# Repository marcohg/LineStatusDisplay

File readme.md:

# Line Status Display
Status indicator from process line encoder

Quadrature encoder signals are captured by a remote modbus rtu 485.  
Modbus client in a embedded pc which sends the data to a graphic output application.

## Add encoder_client simulator
- Script `LineStatusDisplay/fw/encoder_client_01/src/encoder_client.sh` 
- Simulates `/mnt/tmp/encoder_client.status` data for `encoder_gui.py`

## Framework: mount tmpfs, modbus client and Python application
Oct.24/2024  
The init process runs at user (scia) level.  

### Add user `scia` 
- Boot RPi5 as root (marco, pi)
- Add scia:
`marco@raspberry $ sudo useradd -m -c "RPi5 Display" scia`  
use a simple password (will change later)
- Add scia to the following groups: `sudo, audio, video`  
  - `sudo usermod -aG sudo scia`
  - `sudo usermod -aG audio scia`
  - `sudo usermod -aG video scia`

### Allow scia to access the main display
- Boot RPi5
- login ssh to scia, from a host terminal: `ssh scia@192.x.x.x`
- test that scia has sudo operations (like touch /mnt/foo, etc)

#### run raspi-config: `sudo raspi-config`
1. System Options
    - S5. Boot / Auto Login
      - B4. Desktop Autologin (scia has a Desktop GUI)
    - S6. Splash Screen   
      - Yes, splash at boot  (customiza later)
        - `/usr/share/plymouth/themes/pix/splash.png`

### clone LineStatusDisplay
- login scia
- clone repository at /home/scia
  - `git clone https://github.com/marcohg/LineStatusDisplay.git .`
  - project folder is:
    - `/home/scia/LineStatusDisplay`
### install systemd services
  - Change to directory `fw/boot` under project folder
    - First list installed services status using `./list.sh`
    - `sudo ./remove scia` all or `sudo ./remove especific.service`
    - The `./install` will install services for current user

### Monitor Processes initiated bt systemd
- `df -h ` verify the tmpfs mounted partion at `/mnt/tmp`
In this RAM parition, some files are created by the different processes.
- `tail -F /mnt/tmp/encoder_client.status` display the activity of the encoder
 client (ctr-c to end). If the RPi5 communicates with the encoder node, 
 `1729992270,0,71,-2,0,0` 
  - stamp date in seconds since epoch.
  - status, 
  - 0.1 secs tick, 
  - total counts, 
  - delta counts and 
  - frequency.

### Configuration
The file `configuration.json` is created at user's home, WIP

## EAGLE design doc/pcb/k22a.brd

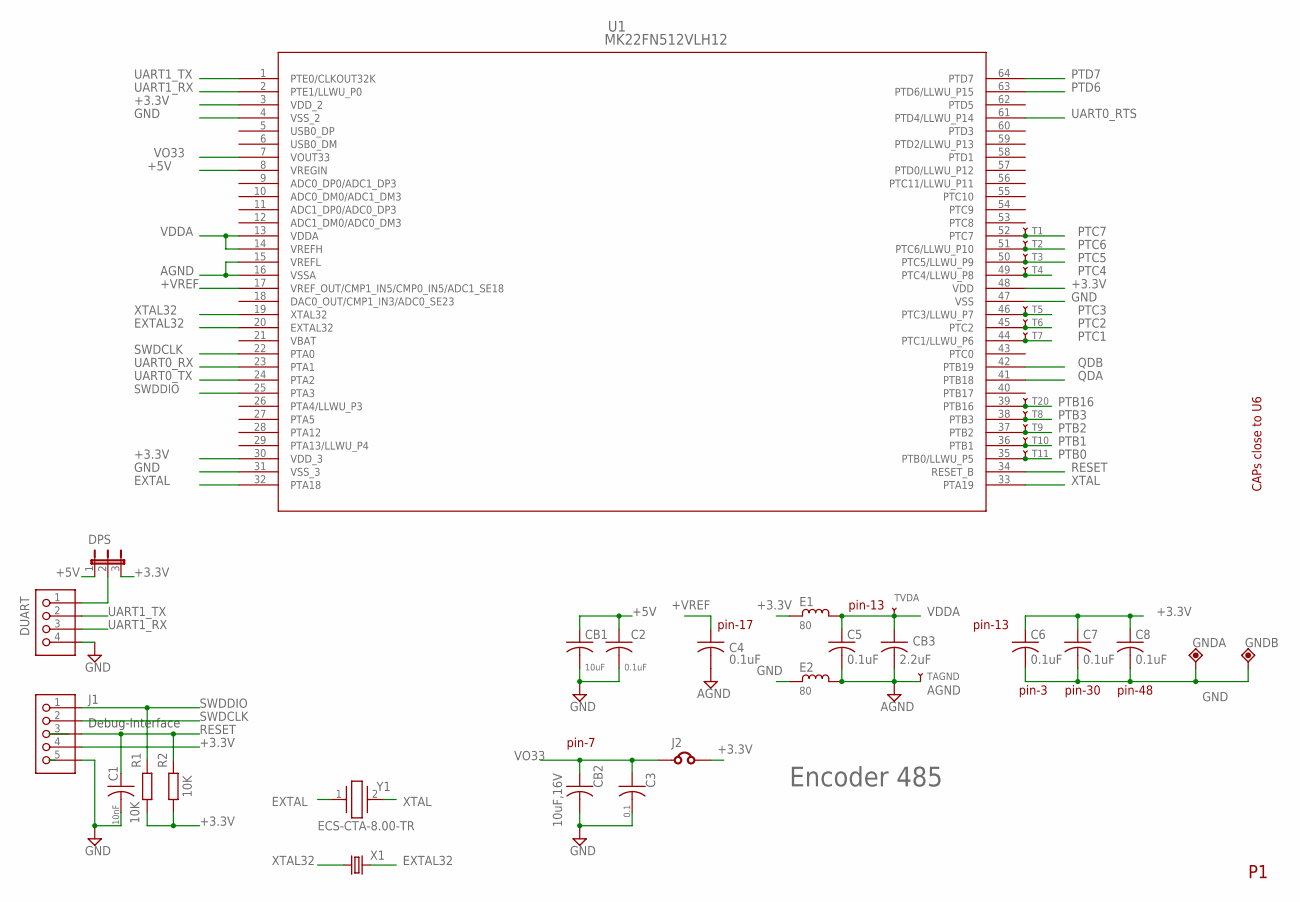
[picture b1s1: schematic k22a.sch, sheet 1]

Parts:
C1: 10nF; C1206
C2, C4, C5, C6, C7, C8: 0.1uF; C1206
C3: 0.1; C1206
CB1: 10uF; C1206
CB2: 10uF,16V; C1206
CB3: 2.2uF; C1206
DPS: JP2E-0805; R0805/2
DUART: PINHD-1X4; 1X4
E1, E2: 80; M1206
GNDA: TPP-PAD-032; PAD-032
GNDB: TPP-PAD-032; PAD-032
J1: PINHD-1X52MM; 1X5_2MM
J2: J0805; R0805
R1, R2: 10K; M1206
T1, T2, T3, T4, T5, T6, T7, T8, T9, T10, T11, T20: ATP-40
TAGND: ATP-40
TVDA: ATP-40
U1: MK22FN512VLH12; LQFP-64_10X10X1.6
X1: CRYSTALTC26V; TC26V@1
Y1: ECS-CTA-8.00-TR; ECSCTA800TR

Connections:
+3.3V: C6.1, C7.1, C8.1, DPS.3, E1.1, J1.4, J2.2, R1.1, R2.1, U1.3 (VDD_2), U1.30 (VDD_3), U1.48 (VDD); also elsewhere on the board
+5V: C2.1, CB1.1, DPS.1, U1.8 (VREGIN); also elsewhere on the board
+VREF: C4.1, U1.17 (VREF_OUT/CMP1_IN5/CMP0_IN5/ADC1_SE18)
AGND: C4.2, C5.2, CB3.2, E2.2, TAGND.P, U1.15 (VREFL), U1.16 (VSSA)
EXTAL: U1.32 (PTA18), Y1.1
EXTAL32: U1.20 (EXTAL32), X1.2
GND: C1.2, C2.2, C3.2, C6.2, C7.2, C8.2, CB1.2, CB2.2, DUART.4, E2.1, GNDA.1, GNDB.1, J1.5, U1.4 (VSS_2), U1.31 (VSS_3), U1.47 (VSS); also elsewhere on the board
unnamed: DPS.2, DUART.1
PTB0: T11.P, U1.35 (PTB0/LLWU_P5)
PTB1: T10.P, U1.36 (PTB1)
PTB2: T9.P, U1.37 (PTB2)
PTB3: T8.P, U1.38 (PTB3)
PTB16: T20.P, U1.39 (PTB16)
PTC1: T7.P, U1.44 (PTC1/LLWU_P6)
PTC2: T6.P, U1.45 (PTC2)
PTC3: T5.P, U1.46 (PTC3/LLWU_P7)
PTC4: T4.P, U1.49 (PTC4/LLWU_P8)
PTC5: T3.P, U1.50 (PTC5/LLWU_P9)
PTC6: T2.P, U1.51 (PTC6/LLWU_P10)
PTC7: T1.P, U1.52 (PTC7)
PTD6: U1.63 (PTD6/LLWU_P15); also elsewhere on the board
PTD7: U1.64 (PTD7); also elsewhere on the board
QDA: U1.41 (PTB18); also elsewhere on the board
QDB: U1.42 (PTB19); also elsewhere on the board
RESET: C1.1, J1.3, R2.2, U1.34 (RESET_B); also elsewhere on the board
SWDCLK: J1.2, U1.22 (PTA0); also elsewhere on the board
SWDDIO: J1.1, R1.2, U1.25 (PTA3); also elsewhere on the board
UART0_RTS: U1.61 (PTD4/LLWU_P14); also elsewhere on the board
UART0_RX: U1.23 (PTA1); also elsewhere on the board
UART0_TX: U1.24 (PTA2); also elsewhere on the board
UART1_RX: DUART.3, U1.2 (PTE1/LLWU_P0)
UART1_TX: DUART.2, U1.1 (PTE0/CLKOUT32K)
VBAT: U1.21 (VBAT)
VDDA: C5.1, CB3.1, E1.2, TVDA.P, U1.13 (VDDA), U1.14 (VREFH)
VO33: C3.1, CB2.1, J2.1, U1.7 (VOUT33)
XTAL: U1.33 (PTA19), Y1.2
XTAL32: U1.19 (XTAL32), X1.1

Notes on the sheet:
Debug-Interface
CAPs close to U6
Encoder 485
pin-13
pin-3
pin-7
pin-48
pin-30
pin-17

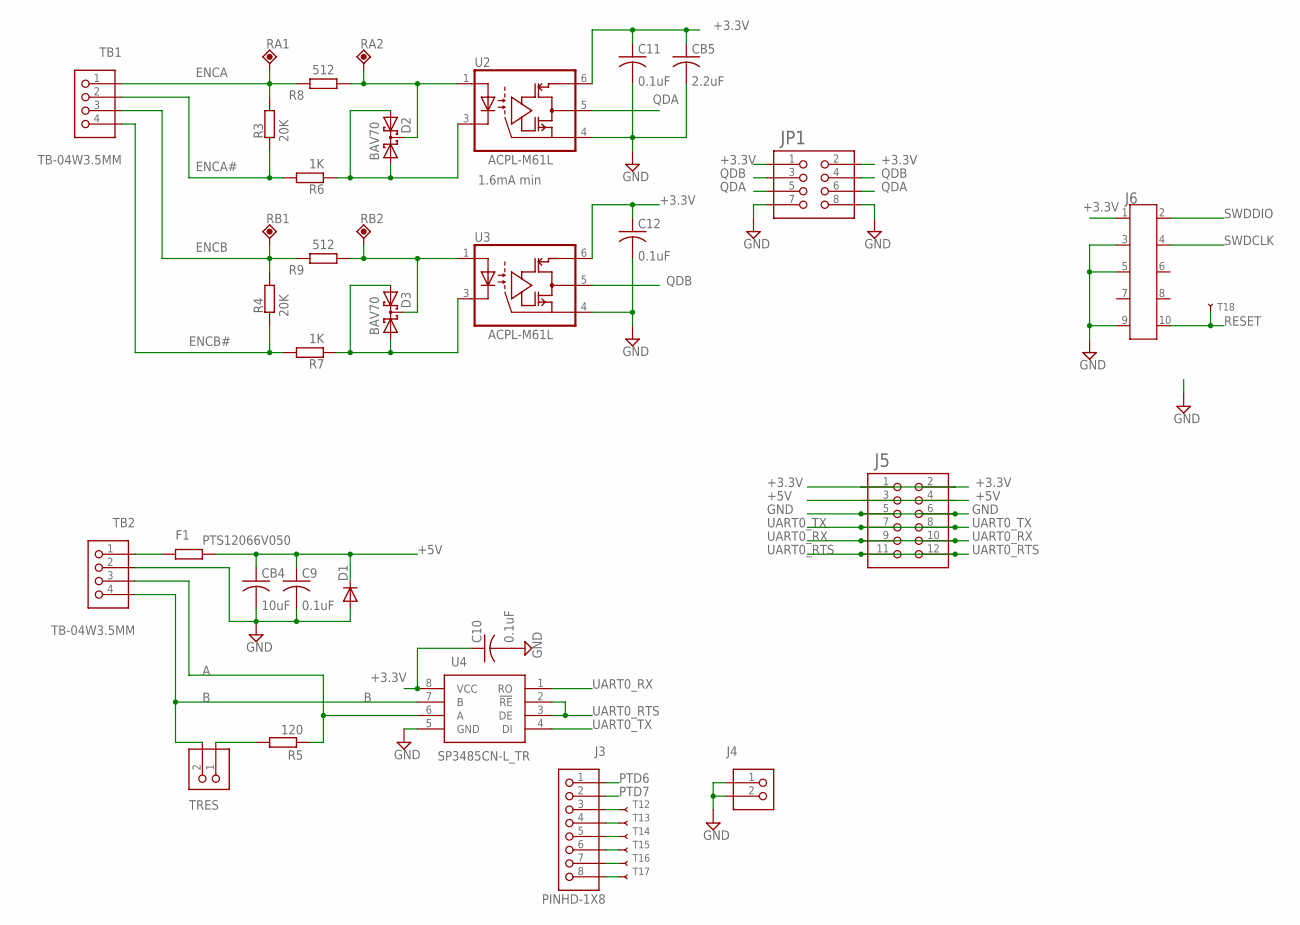
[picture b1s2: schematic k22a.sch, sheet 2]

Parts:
C9, C10, C11, C12: 0.1uF; C1206
CB4: 10uF; C1206
CB5: 2.2uF; C1206
D1: DIODE-DO214AC; DO214AC
D2, D3: BAV70; SOT23; PARTNO BAV70-7-F
F1: PTS12066V050; R1206
J3: PINHD-1X8; 1X8
J4: PINHD-1X2; 1X2
J5: PINHD-2X6; 2X6
J6: FTSH-105-01-L-DVMH; CON10_2X5_FTSH_1
JP1: PINHD-2X4; 2X4
R3, R4: 20K; M1206
R5: 120; M0805; PARTNO RC0805FR-072K7L
R6, R7: 1K; M1206
R8, R9: 512; M1206
RA1, RA2: TPP-PAD-032; PAD-032
RB1, RB2: TPP-PAD-032; PAD-032
T12, T13, T14, T15, T16, T17, T18: ATP-40
TB1, TB2: TB-04W3.5MM; WURTH35-04
TRES: PINHD-1X2; 1X2
U2, U3: ACPL-M61L; SO-5; PARTNO ACPL-M61L-000E
U4: SP3485CN-L_TR; SOIC127P600X175-8N

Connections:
+3.3V: C10.1, C11.1, C12.1, CB5.1, J5.1, J5.2, J6.1, JP1.1, JP1.2, U2.6 (VCC), U3.6 (VCC), U4.8 (VCC); also elsewhere on the board
+5V: C9.1, CB4.1, D1.C, F1.2, J5.3, J5.4; also elsewhere on the board
A: R5.1, TB2.3, U4.6 (A)
B: TB2.4, TRES.2, U4.7 (B)
ENCA: R3.1, R8.2, RA1.1, TB1.1
ENCA#: R3.2, R6.1, TB1.2
ENCB: R4.1, R9.2, RB1.1, TB1.3
ENCB#: R4.2, R7.1, TB1.4
GND: C9.2, C10.2, C11.2, C12.2, CB4.2, CB5.2, D1.A, J4.1, J4.2, J5.5, J5.6, J6.3, J6.5, J6.9, JP1.7, JP1.8, TB2.2, U2.4 (GND), U3.4 (GND), U4.5 (GND); also elsewhere on the board
unnamed: D3.3 (C), R9.1, RB2.1, U3.1 (A)
unnamed: D2.1 (A1), D2.2 (A2), R6.2, U2.3 (C)
unnamed: D2.3 (C), R8.1, RA2.1, U2.1 (A)
unnamed: D3.1 (A1), D3.2 (A2), R7.2, U3.3 (C)
unnamed: F1.1, TB2.1
unnamed: J3.3, T12.P
unnamed: J3.4, T13.P
unnamed: J3.5, T14.P
unnamed: R5.2, TRES.1
unnamed: J3.6, T15.P
unnamed: J3.7, T16.P
unnamed: J3.8, T17.P
PTD6: J3.1; also elsewhere on the board
PTD7: J3.2; also elsewhere on the board
QDA: JP1.5, JP1.6, U2.5 (OUT); also elsewhere on the board
QDB: JP1.3, JP1.4, U3.5 (OUT); also elsewhere on the board
RESET: J6.10, T18.P; also elsewhere on the board
SWDCLK: J6.4; also elsewhere on the board
SWDDIO: J6.2; also elsewhere on the board
UART0_RTS: J5.11, J5.12, U4.2 (!RE), U4.3 (DE); also elsewhere on the board
UART0_RX: J5.9, J5.10, U4.1 (RO); also elsewhere on the board
UART0_TX: J5.7, J5.8, U4.4 (DI); also elsewhere on the board

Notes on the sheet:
1.6mA min

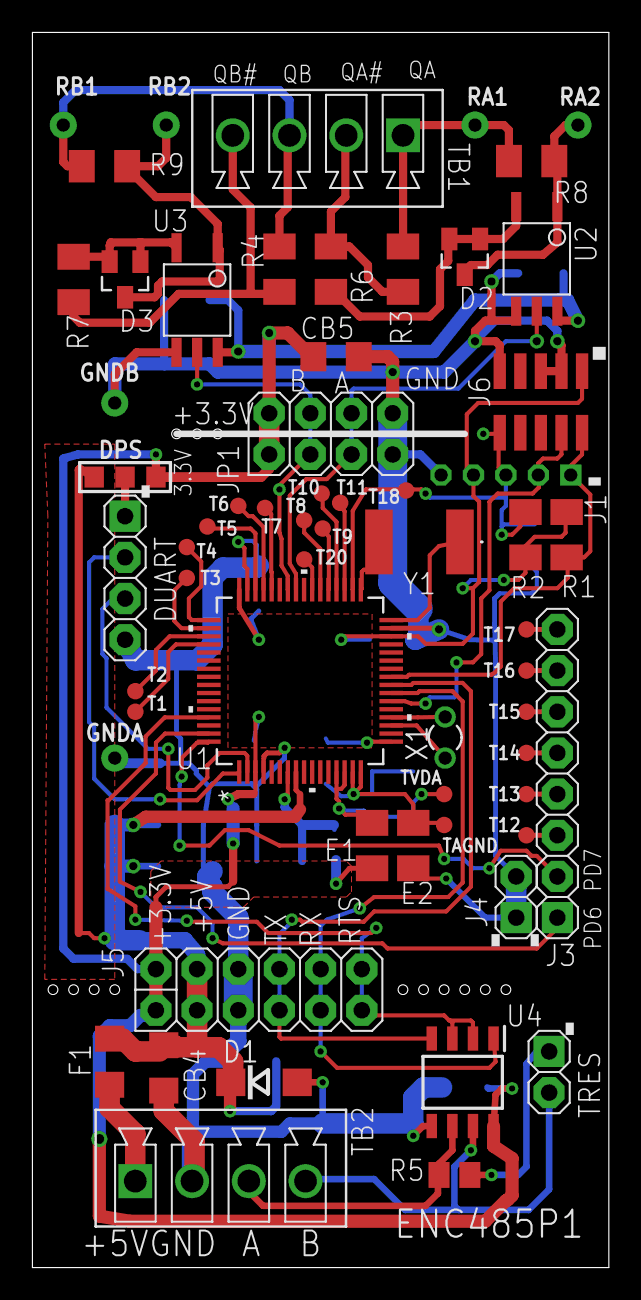
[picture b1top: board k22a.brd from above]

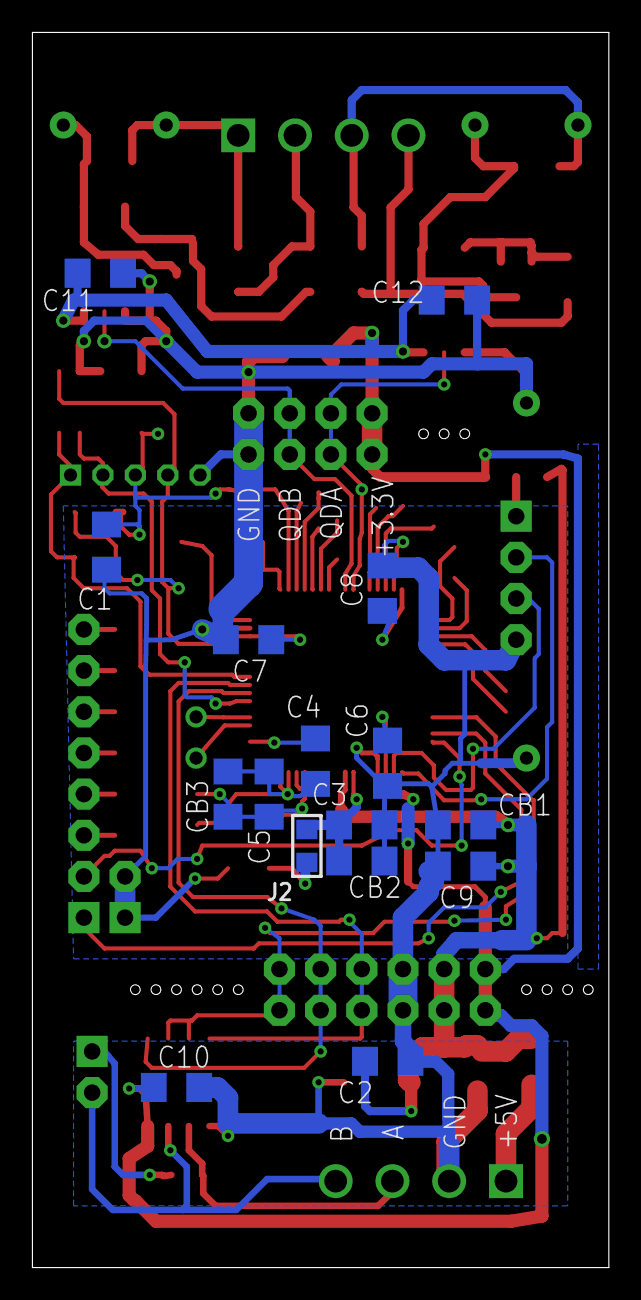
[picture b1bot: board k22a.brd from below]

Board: 2 copper layers, 35.6 x 76.2 mm, 77 parts (16 on the bottom side), 54 nets.

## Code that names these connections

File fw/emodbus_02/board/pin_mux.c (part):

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processor_version: 16.3.0
pin_labels:
- {pin_num: '22', pin_signal: PTA0/UART0_CTS_b/FTM0_CH5/JTAG_TCLK/SWD_CLK/EZP_CLK, label: 'J11[4]/SWD_CLK_TGTMCU'}
- {pin_num: '23', pin_signal: PTA1/UART0_RX/FTM0_CH6/JTAG_TDI/EZP_DI, label: 'J2[4]/RED_LED', identifier: LEDRGB_RED}
- {pin_num: '24', pin_signal: PTA2/UART0_TX/FTM0_CH7/JTAG_TDO/TRACE_SWO/EZP_DO, label: 'J1[8]/GREEN_LED', identifier: LEDRGB_GREEN}
- {pin_num: '25', pin_signal: PTA3/UART0_RTS_b/FTM0_CH0/JTAG_TMS/SWD_DIO, label: 'J11[2]/SWD_DIO_TGTMCU'}
- {pin_num: '26', pin_signal: PTA4/LLWU_P3/FTM0_CH1/NMI_b/EZP_CS_b, label: 'J1[10]/LLWU_P3'}
- {pin_num: '27', pin_signal: PTA5/USB_CLKIN/FTM0_CH2/I2S0_TX_BCLK/JTAG_TRST_b, label: 'J1[1]/I2S0_TX_BCLK', identifier: AC_I2S_SCLK;USB_CLKIN}
- {pin_num: '28', pin_signal: PTA12/FTM1_CH0/I2S0_TXD0/FTM1_QD_PHA, label: 'J1[5]/I2S0_TXD0', identifier: AC_I2S_DIN}
- {pin_num: '29', pin_signal: PTA13/LLWU_P4/FTM1_CH1/I2S0_TX_FS/FTM1_QD_PHB, label: 'J1[3]', identifier: AC_I2S_LRCLK}
- {pin_num: '32', pin_signal: EXTAL0/PTA18/FTM0_FLT2/FTM_CLKIN0, label: 'Y1[3]/EXTAL', identifier: EXTAL0}
- {pin_num: '33', pin_signal: XTAL0/PTA19/FTM1_FLT0/FTM_CLKIN1/LPTMR0_ALT1, label: 'Y1[1]/XTAL', identifier: XTAL0}
- {pin_num: '35', pin_signal: ADC0_SE8/ADC1_SE8/PTB0/LLWU_P5/I2C0_SCL/FTM1_CH0/FTM1_QD_PHA, label: 'J24[2]/LLWU_P5'}
- {pin_num: '36', pin_signal: ADC0_SE9/ADC1_SE9/PTB1/I2C0_SDA/FTM1_CH1/FTM1_QD_PHB, label: 'J24[4]'}
- {pin_num: '37', pin_signal: ADC0_SE12/PTB2/I2C0_SCL/UART0_RTS_b/FTM0_FLT3, label: 'J24[12]/U8[4]/ADC0_SE12/I2C0_SCL/AUD/ACCEL_I2C/POT_5K', identifier: ACCEL_SCL;AUDIO_SCL;POT_5K}
- {pin_num: '38', pin_signal: ADC0_SE13/PTB3/I2C0_SDA/UART0_CTS_b/FTM0_FLT0, label: 'J24[10]/U8[6]/ADC0_SE13/I2C0_SDA/AUD/ACCEL_I2C', identifier: ACCEL_SDA;AUDIO_SDA}
- {pin_num: '39', pin_signal: PTB16/SPI1_SOUT/UART0_RX/FTM_CLKIN0/EWM_IN, label: 'J1[6]/J8[G1]/SD_CARD_DETECT', identifier: SD_CARD_DETECT}
- {pin_num: '40', pin_signal: PTB17/SPI1_SIN/UART0_TX/FTM_CLKIN1/EWM_OUT_b, label: PUSH_BUTTON1, identifier: SW3}
- {pin_num: '41', pin_signal: PTB18/FTM2_CH0/I2S0_TX_BCLK/FTM2_QD_PHA, label: 'J1[12]'}
- {pin_num: '42', pin_signal: PTB19/FTM2_CH1/I2S0_TX_FS/FTM2_QD_PHB, label: 'J2[2]'}
- {pin_num: '43', pin_signal: ADC0_SE14/PTC0/SPI0_PCS4/PDB0_EXTRG/USB_SOF_OUT, label: 'J2[5]/U13[3]'}
- {pin_num: '44', pin_signal: ADC0_SE15/PTC1/LLWU_P6/SPI0_PCS3/UART1_RTS_b/FTM0_CH0/I2S0_TXD0/LPUART0_RTS_b, label: 'J24[6]/LLWU_P6/ADC0_SE15/PUSH_BUTTON2', identifier: SW2}
- {pin_num: '45', pin_signal: ADC0_SE4b/CMP1_IN0/PTC2/SPI0_PCS2/UART1_CTS_b/FTM0_CH1/I2S0_TX_FS/LPUART0_CTS_b, label: 'J24[8]'}
- {pin_num: '51', pin_signal: CMP0_IN0/PTC6/LLWU_P10/SPI0_SOUT/PDB0_EXTRG/I2S0_RX_BCLK/I2S0_MCLK, label: 'J1[16]/LLWU_P10'}
- {pin_num: '49', pin_signal: PTC4/LLWU_P8/SPI0_PCS0/UART1_TX/FTM0_CH3/CMP1_OUT/LPUART0_TX, label: 'J8[P2]/J24[9]/uSD_card_CS', identifier: SD_CARD_DAT3}
- {pin_num: '50', pin_signal: PTC5/LLWU_P9/SPI0_SCK/LPTMR0_ALT2/I2S0_RXD0/CMP0_OUT/FTM0_CH2, label: 'J1[15]/I2S0_RXD0', identifier: AC_I2S_DOUT}
- {pin_num: '52', pin_signal: CMP0_IN1/PTC7/SPI0_SIN/USB_SOF_OUT/I2S0_RX_FS, label: 'J1[11]/I2S0_RX_FS'}
- {pin_num: '53', pin_signal: ADC1_SE4b/CMP0_IN2/PTC8/I2S0_MCLK, label: 'J1[7]/I2S0_MCLK', identifier: AC_SYS_MCLK}
- {pin_num: '54', pin_signal: ADC1_SE5b/CMP0_IN3/PTC9/I2S0_RX_BCLK/FTM2_FLT0, label: 'J1[9]/I2S0_RX_BCLK'}
- {pin_num: '55', pin_signal: ADC1_SE6b/PTC10/I2C1_SCL/I2S0_RX_FS, label: 'J1[13]/I2C1_SCL/I2S0_RX_FS'}
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- {pin_num: '60', pin_signal: PTD3/SPI0_SIN/UART2_TX/LPUART0_TX/I2C0_SDA, label: 'J1[4]/J8[P7]/SPI0_SIN/uSD_SPI_MISO', identifier: SD_CARD_DAT0}
- {pin_num: '61', pin_signal: PTD4/LLWU_P14/SPI0_PCS1/UART0_RTS_b/FTM0_CH4/EWM_IN/SPI1_PCS0, label: 'J2[6]/SPI0_PCS1/LLWU_P14', identifier: RF_CS}
- {pin_num: '62', pin_signal: ADC0_SE6b/PTD5/SPI0_PCS2/UART0_CTS_b/FTM0_CH5/EWM_OUT_b/SPI1_SCK, label: 'J2[12]/BLUE_LED', identifier: LEDRGB_BLUE}
- {pin_num: '63', pin_signal: ADC0_SE7b/PTD6/LLWU_P15/SPI0_PCS3/UART0_RX/FTM0_CH6/FTM0_FLT0/SPI1_SOUT, label: 'J2[8]'}
- {pin_num: '64', pin_signal: PTD7/UART0_TX/FTM0_CH7/FTM0_FLT1/SPI1_SIN, label: 'J2[10]'}
- {pin_num: '1', pin_signal: ADC1_SE4a/PTE0/CLKOUT32K/SPI1_PCS1/UART1_TX/I2C1_SDA/RTC_CLKOUT, label: 'J2[18]/UART1_TX_TGTMCU', identifier: DEBUG_UART_TX;RTC_CLKOUT;CLKOUT32K}
- {pin_num: '2', pin_signal: ADC1_SE5a/PTE1/LLWU_P0/SPI1_SOUT/UART1_RX/I2C1_SCL/SPI1_SIN, label: 'J2[20]/UART1_RX_TGTMCU', identifier: DEBUG_UART_RX}
- {pin_num: '4', pin_signal: VSS4, label: GND}
- {pin_num: '31', pin_signal: VSS31, label: GND}
- {pin_num: '47', pin_signal: VSS47, label: GND}
- {pin_num: '16', pin_signal: VSSA, label: VSSA}
- {pin_num: '15', pin_signal: VREFL, label: VREFL}
- {pin_num: '14', pin_signal: VREFH, label: 'J2[16]/VREFH'}
- {pin_num: '19', pin_signal: XTAL32, label: XTAL32_RTC, identifier: XTAL32}
- {pin_num: '20', pin_signal: EXTAL32, label: EXTAL32_RTC, identifier: EXTAL32}
- {pin_num: '11', pin_signal: ADC1_DP0/ADC0_DP3, label: 'J24[5]/ADC0_DP3/ADC0_SE3/LIGHT_SNSR', identifier: LSENSE_EMITTER}
- {pin_num: '18', pin_signal: DAC0_OUT/CMP1_IN3/ADC0_SE23, label: 'J24[11]/DAC0_OUT/ADC0_SE23'}
- {pin_num: '12', pin_signal: ADC1_DM0/ADC0_DM3, label: 'J24[7]/ADC0_DM3/ADC0_SE7a'}
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- {pin_num: '6', pin_signal: USB0_DM, label: USB_DN, identifier: USB_DN}
- {pin_num: '34', pin_signal: RESET_b, label: 'J11[10]/RST_TGTMCU_b'}
- {pin_num: '8', pin_signal: VREGIN, label: P5V_K22F, identifier: USB_VREGIN}
- {pin_num: '46', pin_signal: CMP1_IN1/PTC3/LLWU_P7/SPI0_PCS1/UART1_RX/FTM0_CH2/CLKOUT/I2S0_TX_BCLK/LPUART0_RX, label: 'J1[14]', identifier: CLKOUT}
 * BE CAREFUL MODIFYING THIS COMMENT - IT IS YAML SETTINGS FOR TOOLS ***********
 */
/* clang-format on */
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BOARD_InitPins:
- options: {callFromInitBoot: 'true', prefix: BOARD_, coreID: core0, enableClock: 'true'}
- pin_list:
  - {pin_num: '24', peripheral: UART0, signal: TX, pin_signal: PTA2/UART0_TX/FTM0_CH7/JTAG_TDO/TRACE_SWO/EZP_DO, identifier: ''}
  - {pin_num: '23', peripheral: UART0, signal: RX, pin_signal: PTA1/UART0_RX/FTM0_CH6/JTAG_TDI/EZP_DI, identifier: ''}
  - {pin_num: '61', peripheral: UART0, signal: RTS, pin_signal: PTD4/LLWU_P14/SPI0_PCS1/UART0_RTS_b/FTM0_CH4/EWM_IN/SPI1_PCS0}
  - {pin_num: '41', peripheral: FTM2, signal: 'QD_PH, A', pin_signal: PTB18/FTM2_CH0/I2S0_TX_BCLK/FTM2_QD_PHA}
  - {pin_num: '42', peripheral: FTM2, signal: 'QD_PH, B', pin_signal: PTB19/FTM2_CH1/I2S0_TX_FS/FTM2_QD_PHB}
  - {pin_num: '52', peripheral: GPIOC, signal: 'GPIO, 7', pin_signal: CMP0_IN1/PTC7/SPI0_SIN/USB_SOF_OUT/I2S0_RX_FS, direction: OUTPUT}
 * BE CAREFUL MODIFYING THIS COMMENT - IT IS YAML SETTINGS FOR TOOLS ***********
 */
/* clang-format on */
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        .pinDirection = kGPIO_DigitalOutput,
        .outputLogic = 0U
    };
    /* Initialize GPIO functionality on pin PTC7 (pin 52)  */
    GPIO_PinInit(GPIOC, 7U, &gpioc_pin52_config);

    /* PORTA1 (pin 23) is configured as UART0_RX */
    PORT_SetPinMux(PORTA, 1U, kPORT_MuxAlt2);

    /* PORTA2 (pin 24) is configured as UART0_TX */
    PORT_SetPinMux(PORTA, 2U, kPORT_MuxAlt2);

    /* PORTB18 (pin 41) is configured as FTM2_QD_PHA */
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    /* PORTB19 (pin 42) is configured as FTM2_QD_PHB */
    PORT_SetPinMux(PORTB, 19U, kPORT_MuxAlt6);

    /* PORTC7 (pin 52) is configured as PTC7 */
    PORT_SetPinMux(PORTC, 7U, kPORT_MuxAsGpio);

    /* PORTD4 (pin 61) is configured as UART0_RTS_b */
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                   /* Mask bits to zero which are setting */
                   (~(SIM_SOPT5_UART0TXSRC_MASK)))

                  /* UART 0 transmit data source select: UART0_TX pin. */
                  | SIM_SOPT5_UART0TXSRC(SOPT5_UART0TXSRC_UART_TX));
}

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BOARD_InitLEDsPins:
- options: {prefix: BOARD_, coreID: core0, enableClock: 'true'}
- pin_list:
  - {pin_num: '23', peripheral: GPIOA, signal: 'GPIO, 1', pin_signal: PTA1/UART0_RX/FTM0_CH6/JTAG_TDI/EZP_DI, direction: OUTPUT, gpio_init_state: 'true', slew_rate: slow,
    open_drain: disable, pull_select: down, pull_enable: disable}
  - {pin_num: '24', peripheral: GPIOA, signal: 'GPIO, 2', pin_signal: PTA2/UART0_TX/FTM0_CH7/JTAG_TDO/TRACE_SWO/EZP_DO, direction: OUTPUT, gpio_init_state: 'true',
    slew_rate: slow, open_drain: disable, pull_select: down, pull_enable: disable}
  - {pin_num: '62', peripheral: GPIOD, signal: 'GPIO, 5', pin_signal: ADC0_SE6b/PTD5/SPI0_PCS2/UART0_CTS_b/FTM0_CH5/EWM_OUT_b/SPI1_SCK, direction: OUTPUT, gpio_init_state: 'true',
    slew_rate: slow, open_drain: disable, drive_strength: low, pull_select: down, pull_enable: disable}
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BOARD_InitButtonsPins:
- options: {prefix: BOARD_, coreID: core0, enableClock: 'true'}
- pin_list:
  - {pin_num: '40', peripheral: GPIOB, signal: 'GPIO, 17', pin_signal: PTB17/SPI1_SIN/UART0_TX/FTM_CLKIN1/EWM_OUT_b, direction: INPUT, slew_rate: fast, open_drain: disable,
    pull_select: up, pull_enable: enable}
  - {pin_num: '44', peripheral: GPIOC, signal: 'GPIO, 1', pin_signal: ADC0_SE15/PTC1/LLWU_P6/SPI0_PCS3/UART1_RTS_b/FTM0_CH0/I2S0_TXD0/LPUART0_RTS_b, direction: INPUT,
    slew_rate: fast, open_drain: disable, pull_select: up, pull_enable: enable}
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
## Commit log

2024-08-17 File organization, Start EncoderModbusPcb
2024-08-23 bsp_01 uart1:debug
2024-08-23 add mex config file
2024-08-24 RX Frame detection using PIT
2024-08-26 Frame detect PIT_CH0, RTS as 485 driver
2024-08-26 Disable RX while sending
2024-08-27 Add FTM2 Quadencoder
2024-08-31 Send k22a proto1 for fab
2024-09-25 Document uart-485 pins
2024-09-25 Added emodbus_02 project
2024-09-25 Add emodbus_02 git_previous logs
2024-09-26 Add encoder client - minimum
2024-10-01 emodbus: 11.0592MHz crystal, client: c_modbus class
2024-10-01 client: thread sleeps 250ms - timeouts
2024-10-01 small changes on RPi5
2024-10-10 Adding systemd described in powerup_seq.md
2024-10-10 Add build_rp5.sh compile script
2024-10-10 This is WIP on ubuntu box
2024-10-10 Correccion de servicios, usr pi
2024-10-19 Test on Ubuntu box Node: Crystal 8MHz, Time tick is 0.1sec encoder_client: elf moved to /usr/local/sbin, valid time-out Add json configuration
2024-10-20 - encoder_client: Refactor, status file regenerated every 100 lines, added epoch - GUI (line_encoder.py): parses client status, manage
2024-10-27 Basic frame work working - shown in status files
2024-11-01 Added encoder_client.sh simulator
2024-12-09 Integrate GUI with encoder - Desktop tested
2024-12-09 Tested on RPI5 configuration.json at HOME

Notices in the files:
parts and their libraries:
testpoint: Copyright (C) 2008, Bob Starr
stanley: COPYRIGHT: Copyright (C) 2015 Accelerated Designs. All rights reserved
